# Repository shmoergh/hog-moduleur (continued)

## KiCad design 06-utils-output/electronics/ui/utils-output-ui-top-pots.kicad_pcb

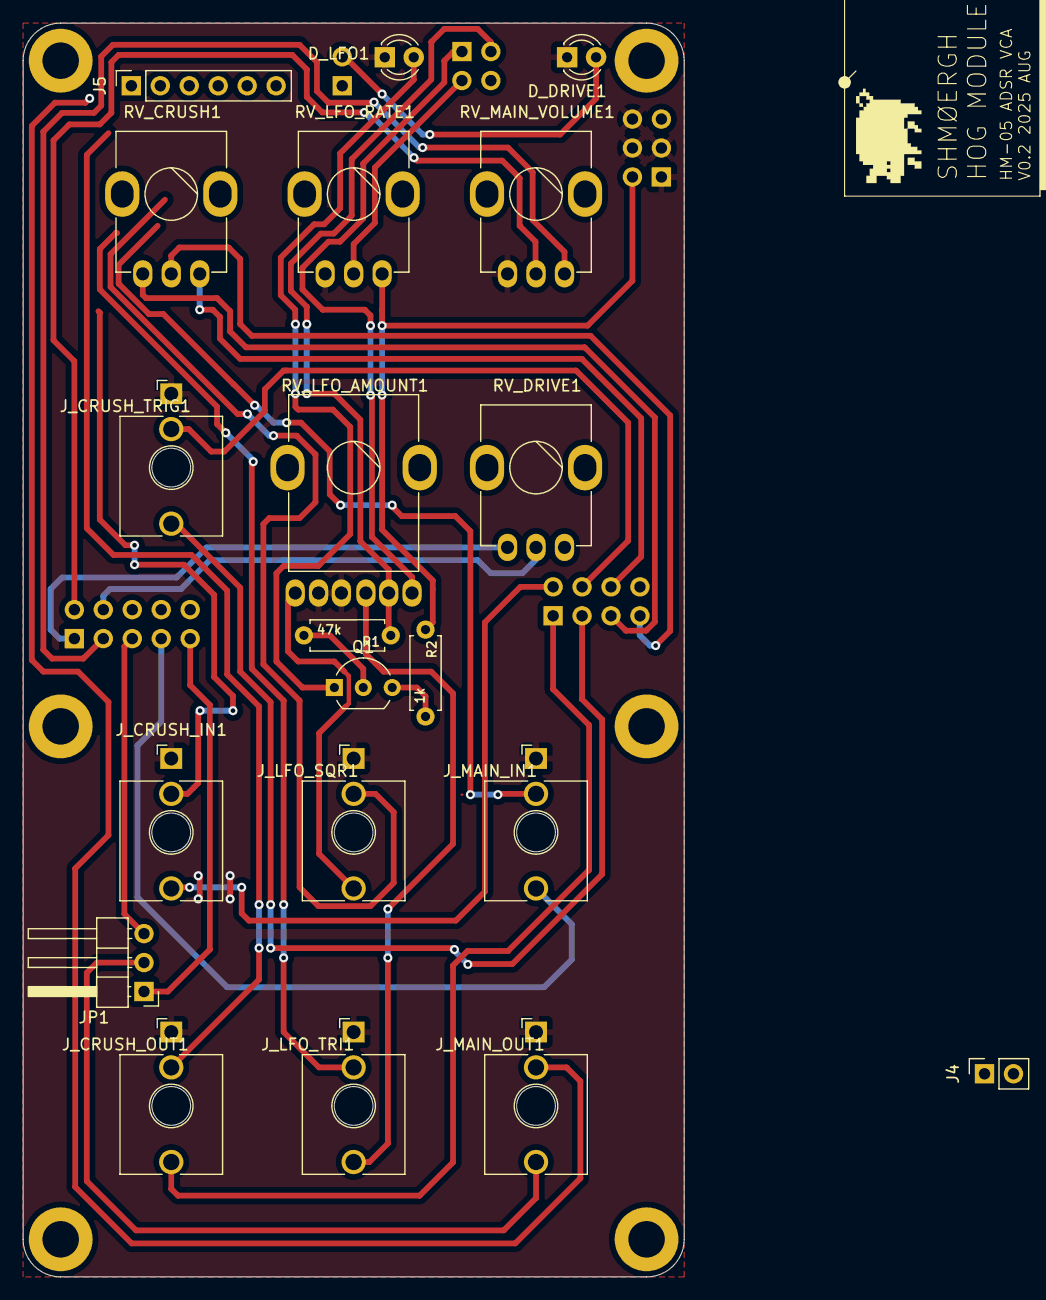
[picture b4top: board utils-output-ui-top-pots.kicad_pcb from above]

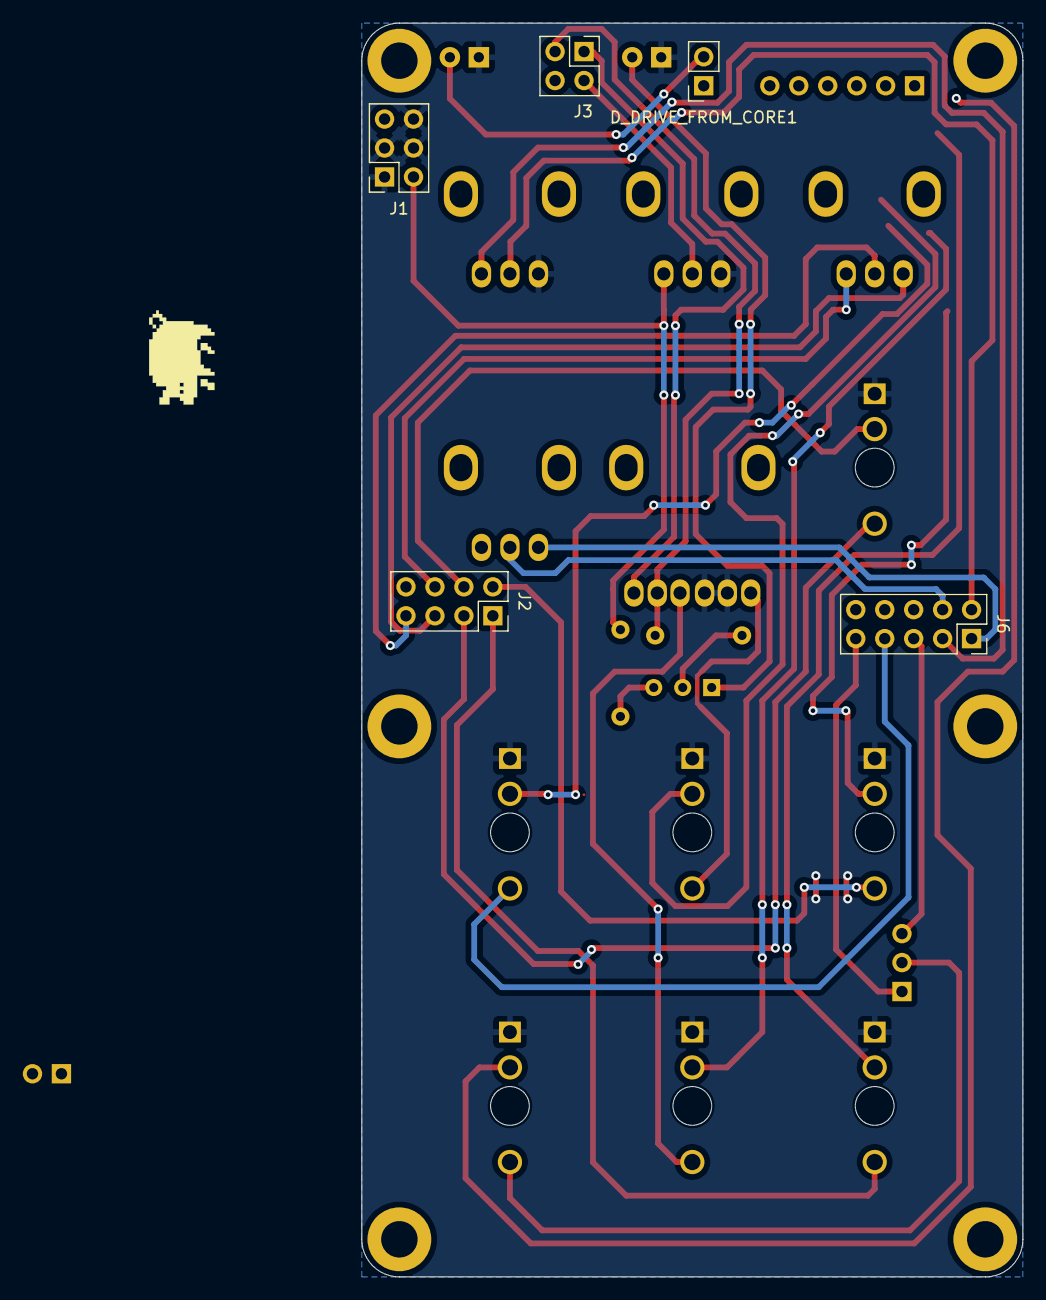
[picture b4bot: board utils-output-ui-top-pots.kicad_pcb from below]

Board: 2 copper layers, 58.0 x 110.0 mm, 31 parts (5 on the bottom side), 32 nets.

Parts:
D_DRIVE1: Red LED; LED_D3.0mm
D_DRIVE_FROM_CORE1: Red LED; PinSocket_1x02_P2.54mm_Vertical
D_LFO1: Red LED; LED_D3.0mm
H1, H2, H3, H4, H5, H6: MountingHole; MountingHole_3.2mm_M3_DIN965_Pad
J1: Conn_02x03_Odd_Even; PinSocket_2x03_P2.54mm_Vertical
J2: Conn_02x04_Odd_Even; PinSocket_2x04_P2.54mm_Vertical
J3: Conn_02x02_Odd_Even; PinSocket_2x02_P2.54mm_Vertical
J4: Conn_01x02; PinSocket_1x02_P2.54mm_Vertical
J5: Conn_01x06; PinSocket_1x06_P2.54mm_Vertical
J6: Conn_02x05_Odd_Even; PinSocket_2x05_P2.54mm_Vertical
JP1: Jumper_3_Open; PinHeader_1x03_P2.54mm_Horizontal
J_CRUSH_IN1: PJ398SM; Jack_3.5mm_QingPu_WQP-PJ398SM_Vertical_CircularHoles
J_CRUSH_OUT1: PJ398SM; Jack_3.5mm_QingPu_WQP-PJ398SM_Vertical_CircularHoles
J_CRUSH_TRIG1: PJ398SM; Jack_3.5mm_QingPu_WQP-PJ398SM_Vertical_CircularHoles
J_LFO_SQR1: PJ398SM; Jack_3.5mm_QingPu_WQP-PJ398SM_Vertical_CircularHoles
J_LFO_TRI1: PJ398SM; Jack_3.5mm_QingPu_WQP-PJ398SM_Vertical_CircularHoles
J_MAIN_IN1: PJ398SM; Jack_3.5mm_QingPu_WQP-PJ398SM_Vertical_CircularHoles
J_MAIN_OUT1: PJ398SM; Jack_3.5mm_QingPu_WQP-PJ398SM_Vertical_CircularHoles
Q1: 2N3904; TO-92_Inline_Wide
R1: 47k; R_Axial_DIN0207_L6.3mm_D2.5mm_P7.62mm_Horizontal
R2: 1k; R_Axial_DIN0207_L6.3mm_D2.5mm_P7.62mm_Horizontal
RV_CRUSH1: 1M; Potentiometer_Bourns_Single-PTV09A
RV_DRIVE1: 100k; Potentiometer_Bourns_Single-PTV09A
RV_LFO_AMOUNT1: A20k; Potentiometer_Bourns_Dual-PTV112-4
RV_LFO_RATE1: A100k; Potentiometer_Bourns_Single-PTV09A
RV_MAIN_VOLUME1: A10k; Potentiometer_Bourns_Single-PTV09A

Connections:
+12V: J1.2, R2.1, RV_LFO_RATE1.3
CRUSH_IN: J2.2, J_CRUSH_IN1.T
CRUSH_IN_DEFAULT: J5.1, J_CRUSH_IN1.TN
CRUSH_OUT: J2.1, J_CRUSH_OUT1.T
CRUSH_OUT_DEFAULT: J5.2, J_CRUSH_OUT1.TN
CRUSH_TRIG: J2.3, J_CRUSH_TRIG1.T
CRUSH_TRIG_DEFAULT: J2.4, J_CRUSH_TRIG1.TN
DRIVE_LED_P: D_DRIVE1.2 (A), D_DRIVE_FROM_CORE1.2 (A)
GND: D_DRIVE1.1 (K), D_LFO1.1 (K), J1.1, J1.3, J1.4, J1.6, J4.1, J4.2, J_CRUSH_IN1.S, J_CRUSH_OUT1.S, J_CRUSH_TRIG1.S, J_LFO_SQR1.S, J_LFO_TRI1.S, J_MAIN_IN1.S, J_MAIN_OUT1.S, RV_LFO_AMOUNT1.1, RV_LFO_AMOUNT1.4, RV_LFO_RATE1.1, RV_MAIN_VOLUME1.1
LFO_RATE: J3.3, RV_LFO_RATE1.2
LFO_SQR: J3.1, RV_LFO_AMOUNT1.3
LFO_SQR_DEFAULT: J5.4, J_LFO_SQR1.TN
LFO_TRI: J3.2, R1.1, RV_LFO_AMOUNT1.6
LFO_TRI_DEFAULT: J5.3, J_LFO_TRI1.TN
unnamed: D_LFO1.2 (A), Q1.1 (E)
unnamed: J_LFO_SQR1.T, RV_LFO_AMOUNT1.2
unnamed: J_LFO_TRI1.T, RV_LFO_AMOUNT1.5
unnamed: Q1.2 (B), R1.2
unnamed: Q1.3 (C), R2.2
OUTPUT_DRIVE_1: J6.1, RV_DRIVE1.1
OUTPUT_DRIVE_3: J6.4, RV_DRIVE1.2, RV_DRIVE1.3
OUTPUT_IN: J6.7, J_MAIN_IN1.T
OUTPUT_IN_DEFAULT: J5.5, J_MAIN_IN1.TN
OUTPUT_LINE_OUT: J6.9, JP1.1 (A)
OUTPUT_OUT: JP1.2 (C), J_MAIN_OUT1.T
OUTPUT_OUT_DEFAULT: J5.6, J_MAIN_OUT1.TN
OUTPUT_PHONES_OUT: J6.5, JP1.3 (B)
OUTPUT_VOL_2: J6.2, RV_MAIN_VOLUME1.2
OUTPUT_VOL_3: J6.3, RV_MAIN_VOLUME1.3
RV_CRUSH_1: J2.5, RV_CRUSH1.1
RV_CRUSH_2: J2.7, RV_CRUSH1.2
RV_CRUSH_3: J2.6, RV_CRUSH1.3
